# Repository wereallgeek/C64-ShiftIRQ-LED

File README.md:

# C64 IRQ+Shift LED

## purpose

When I [built my Mechboard64](https://wereallgeeks.wordpress.com/2025/11/18/commodoremechboard/), I soon realized I didn't like to have the SHIFT-LOCK backlight as a lock indication, so I began using the [IRQ LED module from TEBL](https://github.com/tebl/C64-IRQ-LED), but as [a way to indicate Shift-LOCK on my Mechboard](https://wereallgeeks.wordpress.com/2025/11/27/mechboardled/). This wasn't the first time I used this circuit [for other purposes](https://wereallgeeks.wordpress.com/2023/06/19/cartled/#IRQ) and I was in known territory.

That said, adding this SHIFT-LOCK mod meant I lost the ability to add the [CPU usage indicator](https://wereallgeeks.wordpress.com/2023/04/24/irqmod/) and that is a shame as this is a fun mod to add to any commodore.

So I wondered if it is possible to alter the original circuitry to add a 3rd color (RGB LED?) - the power LED (green) remains ON except when the CPU is working (RED) but the caps-lock alters the color when it is activated.

The IRQ LED module is a simple design based on a 74LS04 logic chip.
[Here is the original design by TEBL](https://github.com/tebl/C64-IRQ-LED)

Half the chip turns out not being used, so altering to add another LED wasn't much of a problem.

The original design had the ability for a cut-off switch, but I have never implemented it, so it was removed to make room for the extra resistor for the 3rd color without increasing board size.

## Build and install
Most of the construction is straight forward, just follow the BOM below as well as the notices where you need to make a few decisions. Where do I connect the inputs? Does my RGB LED work?

You need to get a common cathode (*CC*) LED with more than one colour, To fully utilize this mod a tri color one is required so it will likely be RGB. **Don't** solder it into place until you've test-fitted it for length in place inside your C64 case, solder everything else instead.

Note: it is still possible to use this circuit for just 2 color variation and omit the extra parts.

Next step is to remove the old power LED from the computer. The newer RGB LED might be a tight fit for the existing LED mount though it should fit - just apply some pressure on the front to snap it into place. Afterwards, add the module on top - it might stay on there by itself. if it doesn't you'll need to add some double-sided tape to the IC. I personally add some wiring and keep the wiring and board in place with masking tape.

With proper measurements for length of cable between the LED and where the circuit board can be hold, now is a good time to solder everything together. Having made this mod multiple times, I like to have just one connector (not two) on the circuit. Having one make for an easy removal, but there's often issues keeping two connected during assembly. If I stick the board on the upper case, I like to solder the LED wire in place and have a connector for the bottom section; if I stick the board on the bottom half of the computer e.g. on the keyboard, I like to have the LED on a connector. To each their own, YMMV.

The last piece of the puzzle is attaching the whole thing to the C64 motherboard, you can refer to the picture above as this is where I added the wires needed. I'm using a cut-off set of female dupont wires, the easiest is to wire them to the cartridge port and matching the female part of it to the **markings on the board** (pin order has been changed). Looking at the cartridge port as pictured below: 
- Cartridge port Pin 1 goes to GND (J1 pin 1)
- Cartridge port Pin 3 goes to VCC (J1 pin 2)
- Cartridge port Pin 4 goes to IRQ (J1 pin 3)

5V & Ground can be also taken from the Mechboard, along with the shift-lock signal as seen in the picture above.

Before powering up, double-check that GND and VCC is in the correct spot, swapping them around will kill the IC on the IRQ LED board. Enjoy your color-changing green power LED!

# HOW IT WORKS
Of course the sky is the limit - while I am using it for SHIFT-LOCK and IRQ (CPU usage) any signal can be used with this circuitry, have fun with it!

Here is how this thing behaves:
- 5V and GND are what it takes to illuminate the power led. 
- When the IRQ signal is high, the power led will _change_ from its initial color in favor of the second color.
- When the SHIFT-LOCK signal is high, the 3rd color will illuminate _in addition to_ the initial color

giving e.g. green+blue (cyan) and red+blue (purple) instead of green and red while the shift is locked.

This way, the shift lock _alter_ the led color, but the IRQ/ non-IRQ state is still visible

# BOM
Most parts should be easy to get a hold of from your favourite local electronic component shop, but since I don't have access to the more serious ones I'm mostly getting my components from ebay/AliExpress (free shipping most places, but plan on waiting 3-4 weeks though).

| Reference    | Item                                  | Count |
| ------------ | ------------------------------------- | ----- |
| PCB          | Fabricate using Gerber files ([order](https://www.pcbway.com/project/shareproject/Commodore_64_IRQ_Mechboard_Shift_Lock_LED_module_bc6c7e6d.html)) |     1 |
| D1 *         | 5mm RGB LED (common cathode)          |     1 |
| J1           | 4-pin right-angle header pins         |     1 |
| R1,R2,R3     | 330 ohm resistor                      |     3 | 
| U1           | 74LS04 or 74HCT04 (DIP-14)            |     1 |

*) These are 4 pin LEDs of the common cathode variety, check using diode test on a multimeter to ensure that the center pin is GND and that you know which colour goes where. Alternatively, jam a CR2032 battery between the pins. 

## 🛠️ Modifications & Changelog (CERN OHL v1.2 Compliance)

As required by the **CERN Open Hardware Licence v1.2**, here is the list of modifications made to the original design by **TEBL**:

- **3rd Color Integration:** Altered the original circuitry to support a full 3-color RGB LED.
- **Logic Chip Optimization:** Connected the remaining unused gates of the **74LS04** logic IC to successfully monitor and display the Shift-LOCK / Caps-Lock status alongside CPU usage.
- **Form Factor Maintenance:** Removed the optional cut-off switch from the original schematic. This freed up enough space to add the extra resistor required for the 3rd color without increasing the overall size of the PCB.

### ⚠️ Licensing & Attribution Notice
Any derivative work, manufacture, or commercial distribution of this modified board **MUST retain the original credits to [TEBL](https://github.com/tebl/C64-IRQ-LED) and the modification credits to [We're All Geeks](https://github.com/wereallgeek/C64-ShiftIRQ-LED) **. All derivative hardware layouts and code must remain open-source under the CERN OHL v1.2 license terms.

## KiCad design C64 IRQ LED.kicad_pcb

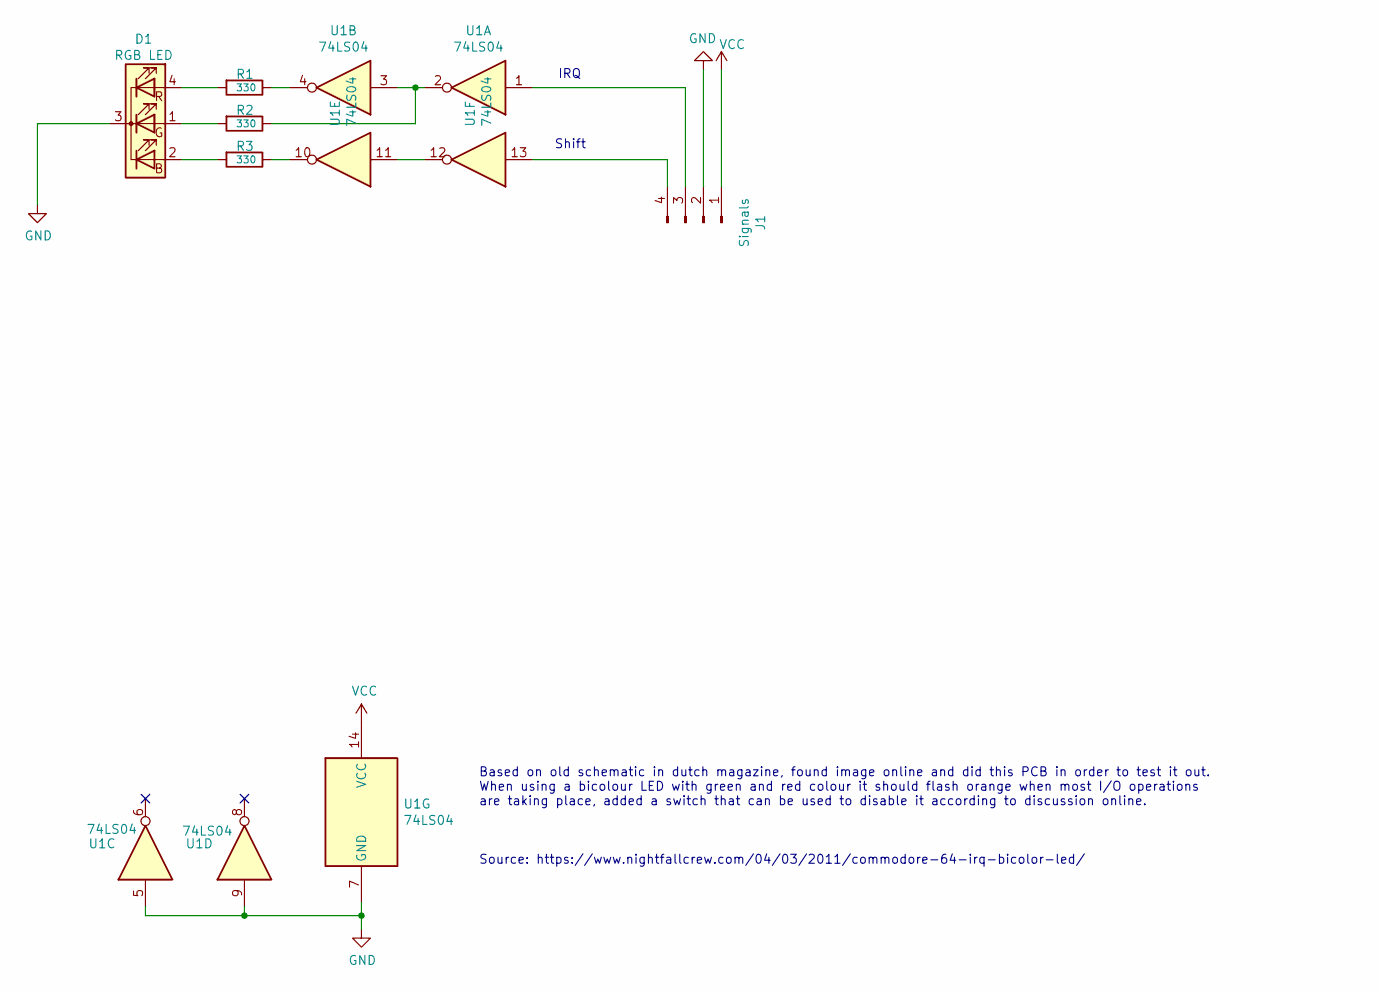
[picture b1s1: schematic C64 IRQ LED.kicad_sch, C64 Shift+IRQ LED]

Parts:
D1: RGB LED; LED_D5.0mm-4_RGB
J1: Signals; PinHeader_1x04_P2.54mm_Horizontal
R1, R2, R3: 330; R_Axial_DIN0207_L6.3mm_D2.5mm_P7.62mm_Horizontal
U1: 74LS04; DIP-14_W7.62mm_LongPads

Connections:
GND: D1.3 (K), J1.2, U1.5, U1.7 (GND), U1.9
unnamed: D1.2 (BA), R3.2
unnamed: D1.1 (GA), R2.2
unnamed: D1.4 (RA), R1.2
unnamed: J1.3, U1.1
unnamed: J1.4, U1.13
unnamed: R1.1, U1.4
unnamed: R2.1, U1.2, U1.3
unnamed: R3.1, U1.10
unnamed: U1.11, U1.12
VCC: J1.1, U1.14 (VCC)

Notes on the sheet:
Based on old schematic in dutch magazine, found image online and did this PCB in order to test it out. When using a bicolour LED with green and red colour it should flash orange when most I/O operations are taking place, added a switch that can be used to disable it according to discussion online.
Source: https://www.nightfallcrew.com/04/03/2011/commodore-64-irq-bicolor-led/
IRQ
Shift

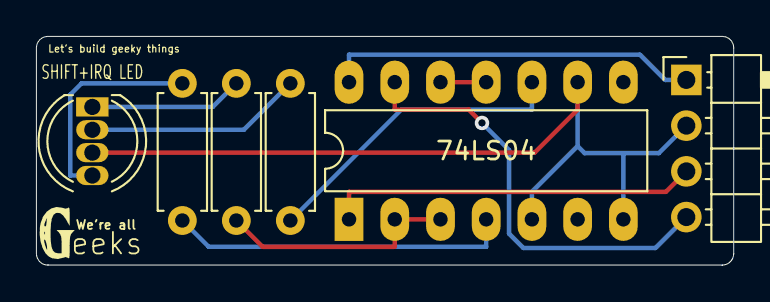
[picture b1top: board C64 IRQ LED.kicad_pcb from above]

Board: 2 copper layers, 38.7 x 12.7 mm, 6 parts (0 on the bottom side), 11 nets.

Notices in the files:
C64 IRQ LED.kicad_pcb:
Licensed under CERN-OHL-S v2
